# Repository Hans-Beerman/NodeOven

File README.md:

**NodeOven**

NodeOven is a node, used at the MakerSpace Leiden, to control a Ceramic oven. This repository has the following subdirs:

- **Drawings:**

Schematic of the wiring between the different modules used

- **KiCad\_files:**

The design of the PCB for the Node/Controller. De PCB in this design is not meant to be used for a real PCB. It is used as guideline for a handmade PCB

- **Photos:**

Some photos of the Node made.

- **PlatformIO\_Files:**

The source code for the Node and the display used. For the development of this software PlatformIO is used, an Extension on Visual Studio Code.

For measuring the oven temperature different types of thermocouples can be used. The configuration of the correct one is done in:

/PlatformIO\_Files/NodeOven/platformio.ini

See for possible types to be used, the comment in this file for THERMOCOUPLE\_TYPE=

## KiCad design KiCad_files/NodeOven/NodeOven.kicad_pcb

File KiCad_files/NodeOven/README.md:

**NodeOven MakerSpace Leiden**

The NodeOven is used to control the ceramic oven of the MakerSpace in Leiden

This repository contains the schematic drawings, made in KiCad for this node.

The PCB in this design is not meant to be used for a real printed circuit board, but is added to be used as a guideline for making the print by hand on a prefab PCB for experimental use.

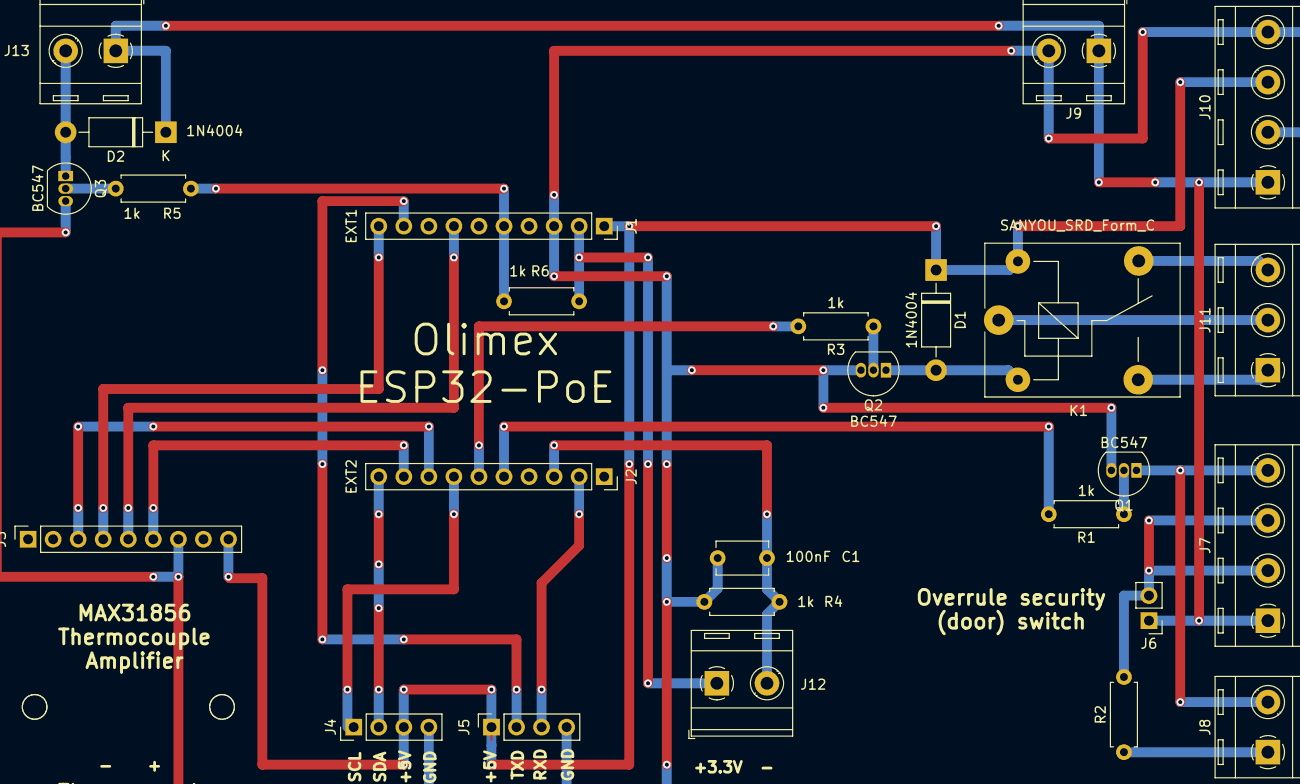
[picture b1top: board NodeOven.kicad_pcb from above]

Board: 2 copper layers, 26 parts (0 on the bottom side), 27 nets.

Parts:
C1: 100nF; C_Disc_D5.1mm_W3.2mm_P5.00mm
D1, D2: 1N4004; D_DO-41_SOD81_P10.16mm_Horizontal
J1: EXT1; PinSocket_1x10_P2.54mm_Vertical
J2: EXT2; PinSocket_1x10_P2.54mm_Vertical
J3: Conn_01x09; PinSocket_1x09_P2.54mm_Vertical
J4: Conn_01x04; PinHeader_1x04_P2.54mm_Vertical
J5: Conn_01x04; PinSocket_1x04_P2.54mm_Vertical
J6: Conn_01x02; PinHeader_1x02_P2.54mm_Vertical
J7, J10: Screw_Terminal_01x04; TerminalBlock_RND_205-00289_1x04_P5.08mm_Horizontal
J8, J9, J12, J13: Screw_Terminal_01x02; TerminalBlock_RND_205-00287_1x02_P5.08mm_Horizontal
J11: Screw_Terminal_01x03; TerminalBlock_RND_205-00288_1x03_P5.08mm_Horizontal
K1: SANYOU_SRD_Form_C; Relay_SPDT_SANYOU_SRD_Series_Form_C
Q1, Q2, Q3: BC547; TO-92_Inline
R1, R2, R3, R4, R5, R6: 1k; R_Axial_DIN0207_L6.3mm_D2.5mm_P7.62mm_Horizontal

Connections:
+3V3: J1.2, J12.1, R6.2
+5V: D1.1, J1.1, J3.9, J4.3, J5.1, J10.3, K1.5
+12V: D2.1, J6.1, J7.1, J9.1, J10.1, J13.1
GND: C1.2, J1.3, J3.7, J4.4, J5.4, J9.2, J10.2, J10.4, Q1.3, Q2.3, Q3.3, R4.1
GPI35: C1.1, J2.3, J12.2, R4.2
GPI36_U1RXD: J2.2, J5.3
GPIO0: J1.5, R5.2, R6.1
GPIO2_HS2_DATA0: J1.7, J3.5
GPIO4_U1TXD: J1.9, J5.2
GPIO5_SPI_C5: J1.10, J3.4
GPIO13_I2C-SDA: J2.10, J4.2
GPIO14_HS2_CLK: J2.9, J3.6
GPIO15_HS2_CMD: J2.8, J3.3
GPIO16_I2C-SCL: J2.7, J4.1
GPIO32: J2.6, R3.2
GPIO33: J2.5, R1.2
unnamed: D1.2, K1.2, Q2.1
unnamed: D2.2, J13.2, Q3.1
unnamed: J6.2, J7.2, J7.3, R2.2
unnamed: J7.4, J8.2, Q1.1
unnamed: J8.1, R2.1
unnamed: J11.1, K1.3
unnamed: J11.2, K1.1
unnamed: J11.3, K1.4
unnamed: Q1.2, R1.1
unnamed: Q2.2, R3.1
unnamed: Q3.2, R5.1

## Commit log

2020-08-10 NodeOven first version
2020-08-11 platformio.ini updated, because library was missing
2020-08-11 Corrected small error in platformio.ini
2020-08-11 Reverted to default (MSL) mqtt server
2020-08-11 Changed platformio.ini files
2020-08-14 Added more libraries to the platformio.ini files
